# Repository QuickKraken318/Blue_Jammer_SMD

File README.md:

Original project: https://github.com/EmenstaNougat/ESP32-BlueJammer

Not tested IRL yet

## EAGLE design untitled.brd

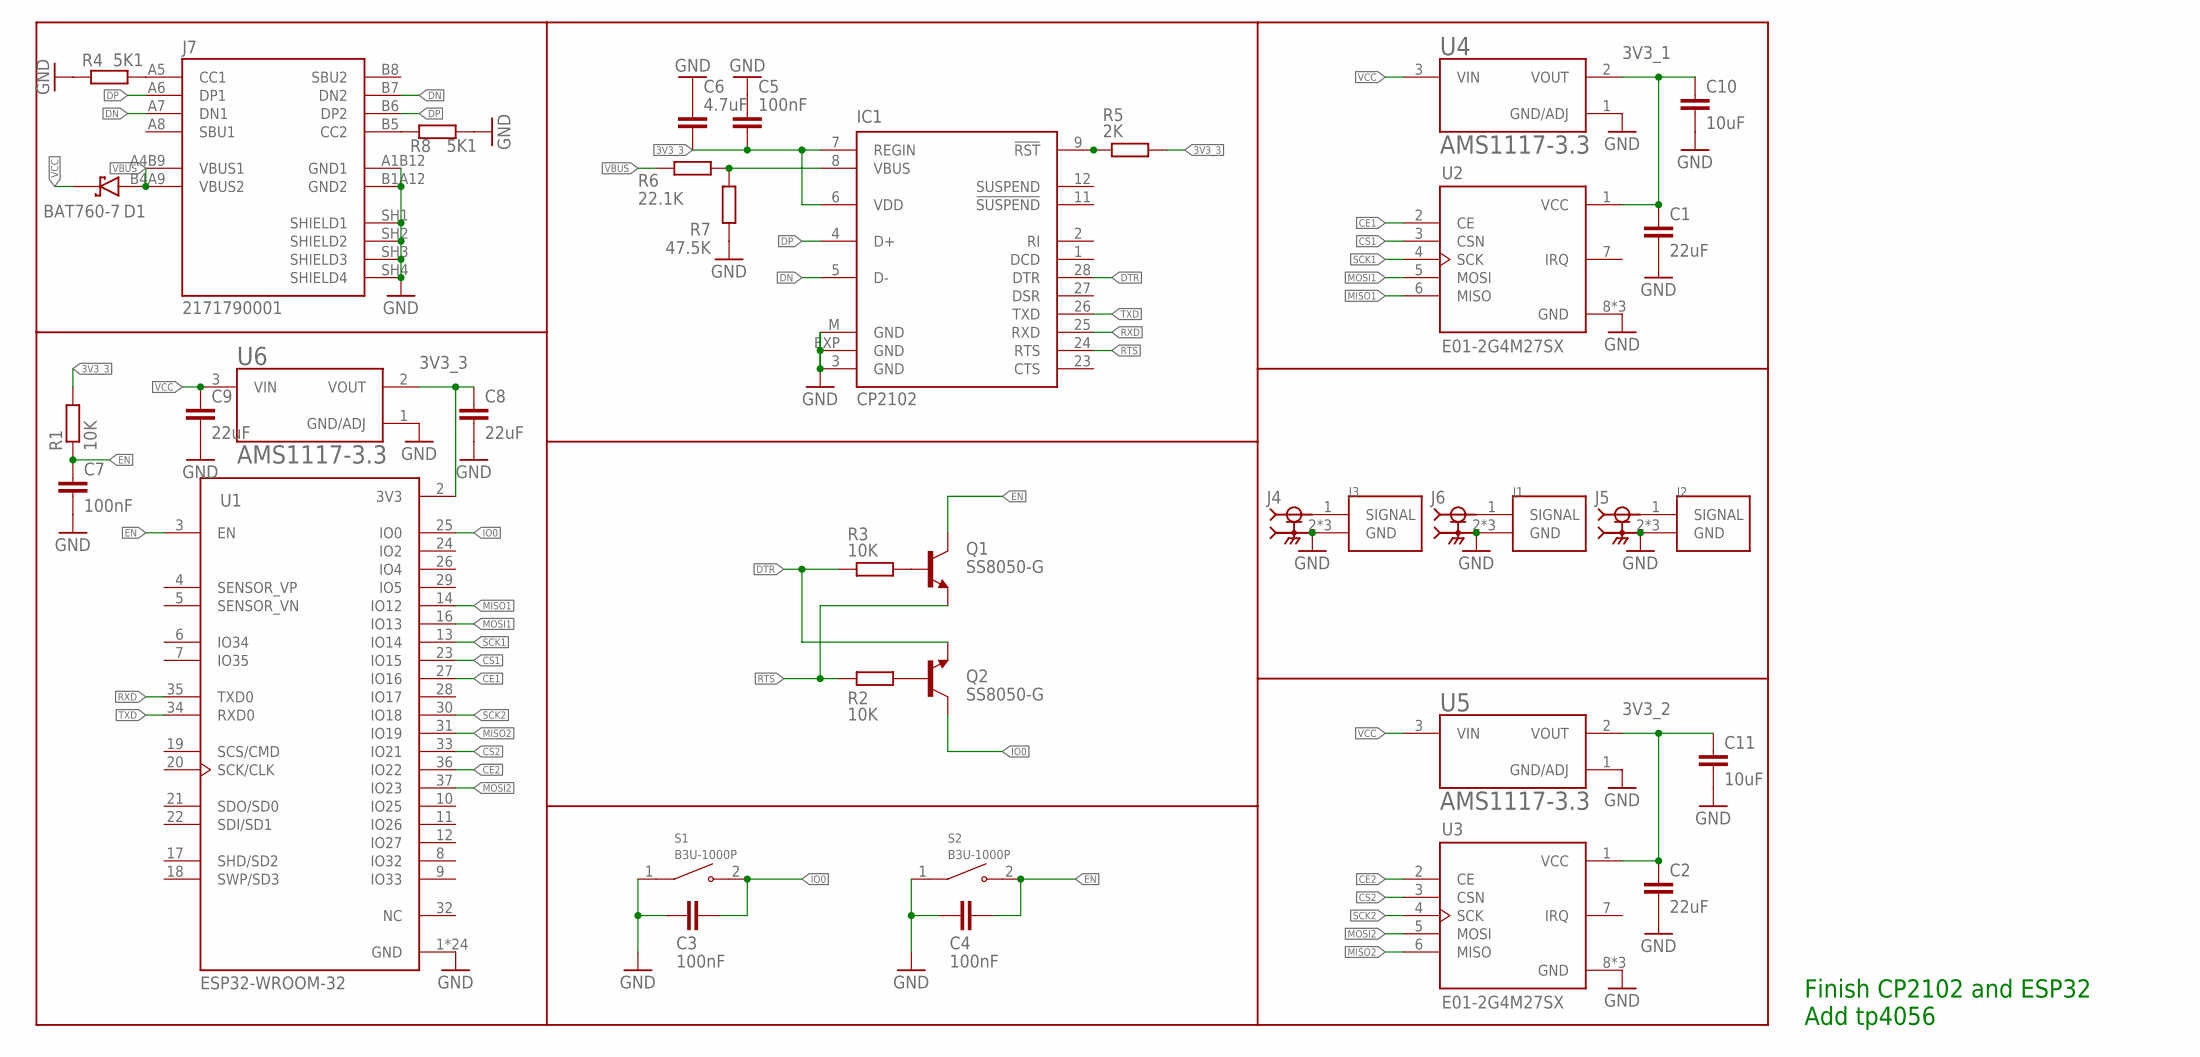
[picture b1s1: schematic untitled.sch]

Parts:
C1, C2, C8, C9: 22uF; C0603
C3, C4, C5, C7: 100nF; C0603
C6: 4.7uF; C0603
C10, C11: 10uF; C0603
D1: BAT760-7; SOD2513X120N
IC1: CP2102; MLP28
J1, J2, J3: RSP-122811-02; SAMTEC_RSP-122811-02
J4, J5, J6: SMA-J-P-X-RA-TH1; SAMTEC_SMA-J-P-X-RA-TH1
J7: 2171790001; MOLEX_2171790001
Q1, Q2: SS8050-G; TRANS_SS8050-G
R1, R2, R3: 10K; R0603
R4, R8: 5K1; R0603
R5: 2K; R0603
R6: 22.1K; R0603
R7: 47.5K; R0603
S1, S2: B3U-1000P; SW_B3U-1000P
U1: ESP32-WROOM-32; MODULE_ESP32-WROOM-32
U2, U3: E01-2G4M27SX; XCVR_E01-2G4M27SX
U4, U5, U6: AMS1117-3.3; SOT229P700X180-4N

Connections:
3V3_1: C1.1, C10.1, U2.1 (VCC), U4.2 (VOUT)
3V3_2: C2.1, C11.1, U3.1 (VCC), U5.2 (VOUT)
3V3_3: C5.2, C6.2, C8.1, IC1.6 (VDD), IC1.7 (REGIN), R1.2, R5.2, U1.2 (3V3), U6.2 (VOUT)
CE1: U1.27 (IO16), U2.2 (CE)
CE2: U1.36 (IO22), U3.2 (CE)
CS1: U1.23 (IO15), U2.3 (CSN)
CS2: U1.33 (IO21), U3.3 (CSN)
DN: IC1.5 (D-), J7.A7 (DN1), J7.B7 (DN2)
DP: IC1.4 (D+), J7.A6 (DP1), J7.B6 (DP2)
DTR: IC1.28 (DTR), Q2.2 (E), R3.1
EN: C4.2, C7.1, Q1.3 (C), R1.1, S2.2, U1.3 (EN)
GND: C1.2, C2.2, C3.1, C4.1, C5.1, C6.1, C7.2, C8.2, C9.2, C10.2, C11.2, IC1.3 (GND), IC1.EXP (GND), IC1.M (GND), J1.2 (GND), J1.3 (GND), J1.4 (GND), J2.2 (GND), J2.3 (GND), J2.4 (GND), J3.2 (GND), J3.3 (GND), J3.4 (GND), J4.2, J4.3 (2), J4.4 (2), J4.5 (2), J5.2, J5.3 (2), J5.4 (2), J5.5 (2), J6.2, J6.3 (2), J6.4 (2), J6.5 (2), J7.A1B12 (GND1), J7.B1A12 (GND2), J7.SH1 (SHIELD1), J7.SH2 (SHIELD2), J7.SH3 (SHIELD3), J7.SH4 (SHIELD4), R4.1, R7.1, R8.2, S1.1, S2.1, U1.1 (GND), U1.15 (GND), U1.38 (GND), U1.39_1 (GND), U1.39_2 (GND), U1.39_3 (GND), U1.39_4 (GND), U1.39_5 (GND), U1.39_6 (GND), U1.39_7 (GND), U1.39_8 (GND), U1.39_9 (GND), U1.39_10 (GND), U1.39_11 (GND), U1.39_12 (GND), U1.39_13 (GND), U1.39_14 (GND), U1.39_15 (GND), U1.39_16 (GND), U1.39_17 (GND), U1.39_18 (GND), U1.39_19 (GND), U1.39_20 (GND), U1.39_21 (GND), U2.8 (GND), U2.9 (GND), U2.10 (GND), U3.8 (GND), U3.9 (GND), U3.10 (GND), U4.1 (GND/ADJ), U5.1 (GND/ADJ), U6.1 (GND/ADJ)
IO0: C3.2, Q2.3 (C), S1.2, U1.25 (IO0)
MISO1: U1.14 (IO12), U2.6 (MISO)
MISO2: U1.31 (IO19), U3.6 (MISO)
MOSI1: U1.16 (IO13), U2.5 (MOSI)
MOSI2: U1.37 (IO23), U3.5 (MOSI)
unnamed: J3.1 (SIGNAL), J4.1
unnamed: J7.A5 (CC1), R4.2
unnamed: J2.1 (SIGNAL), J5.1
unnamed: J7.B5 (CC2), R8.1
unnamed: J1.1 (SIGNAL), J6.1
unnamed: Q1.1 (B), R3.2
unnamed: Q2.1 (B), R2.2
unnamed: IC1.9 (!RST), R5.1
unnamed: IC1.8 (VBUS), R6.2, R7.2
RTS: IC1.24 (RTS), Q1.2 (E), R2.1
RXD: IC1.25 (RXD), U1.35 (TXD0)
SCK1: U1.13 (IO14), U2.4 (SCK)
SCK2: U1.30 (IO18), U3.4 (SCK)
TXD: IC1.26 (TXD), U1.34 (RXD0)
VBUS: D1.A, J7.A4B9 (VBUS1), J7.B4A9 (VBUS2), R6.1
VCC: C9.1, D1.C (K), U4.3 (VIN), U5.3 (VIN), U6.3 (VIN)

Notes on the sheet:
Finish CP2102 and ESP32 Add tp4056

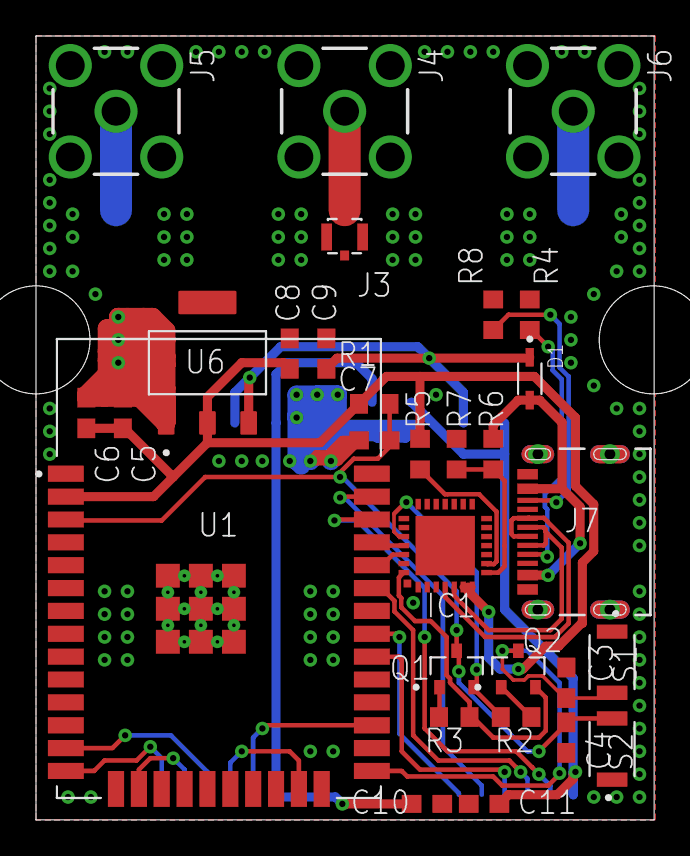
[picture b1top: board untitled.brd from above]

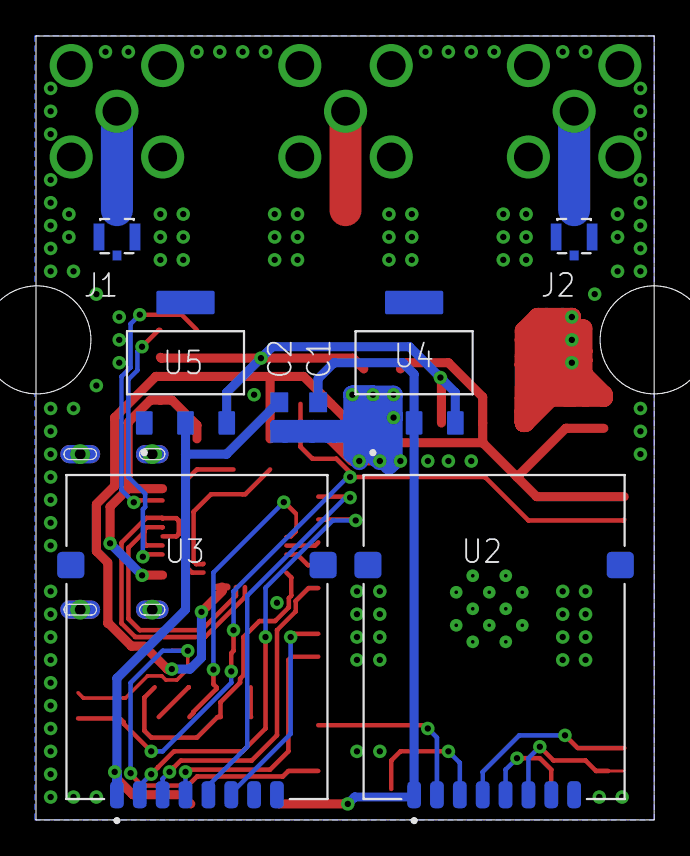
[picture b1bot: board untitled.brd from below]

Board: 2 copper layers, 34.3 x 43.6 mm, 38 parts (8 on the bottom side), 33 nets.
